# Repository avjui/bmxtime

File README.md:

BMXTIME
=======

BMXTIME is a small programm for time measure. The development is in betaphase. The time measure can be done with some lightbarrier build with a Ardurino.

<hr />

Current Features are:

	* time stop 
	* otpional time between
	* add differnt driver for statistic

<hr />

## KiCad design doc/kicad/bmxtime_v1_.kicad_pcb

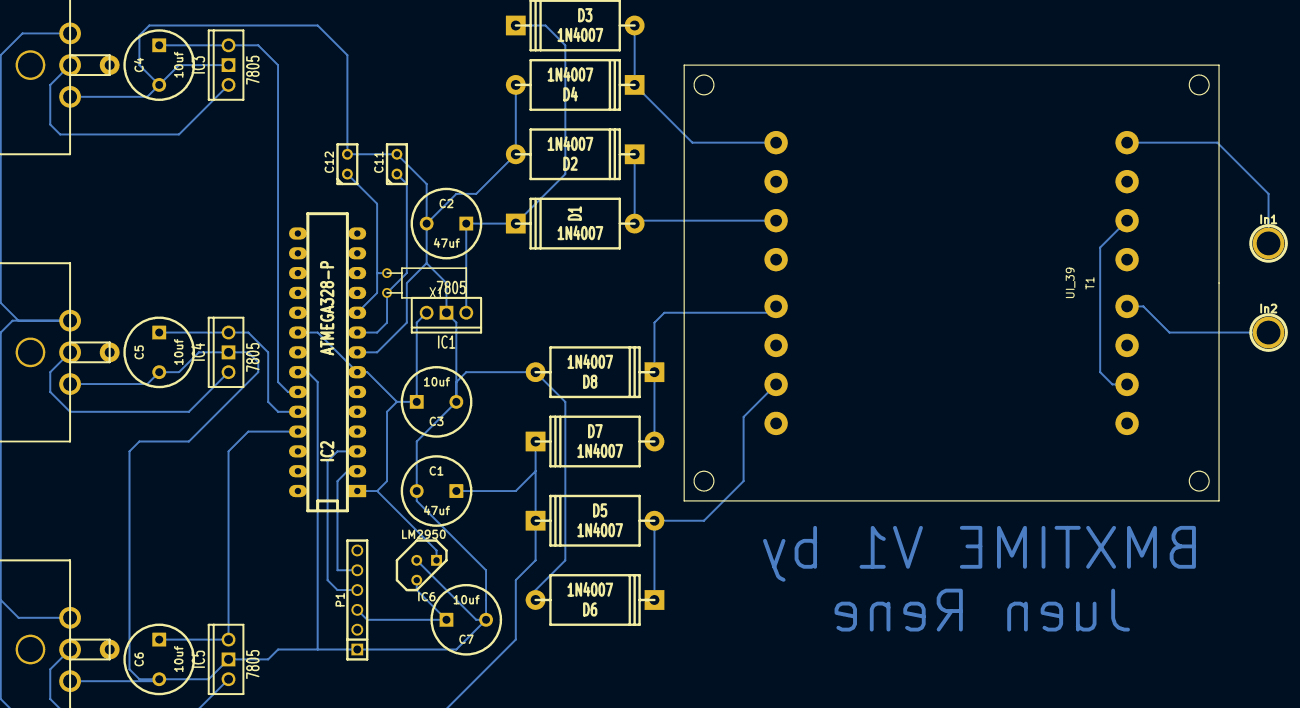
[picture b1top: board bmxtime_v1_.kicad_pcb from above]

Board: 2 copper layers, 31 parts (0 on the bottom side), 22 nets.

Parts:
C1, C2: 47uf; C2V8
C3, C4, C5, C6, C7: 10uf; C2V8
C11, C12: 22pf; C1
D1, D2, D3, D4, D5, D6, D7, D8: 1N4007; D6
IC1, IC3, IC4, IC5: 7805; LM78XXV
IC2: ATMEGA328-P; DIP-28__300_ELL
IC6: LM2950; LM2931
In1, In2: CONN_1; 1pin
K1, K2, K3: XLR3; XLR3MC
P1: CONN_SERIAL_SF; PIN_ARRAY-6X1
T1: UI_39; UI 39_Flachtransformator
X1: 16Mhz; QMONTRE

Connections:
/5V: C3.1, IC1.VO, IC2.1, IC2.7, IC2.20, IC6.1
unnamed: C5.1, IC2.24, IC4.VO
unnamed: D7.1, D8.2, T1.12
unnamed: IC2.3, P1.4
unnamed: C6.1, IC2.25, IC5.VO
unnamed: IC2.2, P1.5
unnamed: C7.1, IC6.2, P1.3
unnamed: D1.1, D2.2, T1.14
unnamed: T1.3, T1.7
unnamed: In2.1, T1.5
unnamed: In1.1, T1.1
unnamed: D5.1, D6.2, T1.10
unnamed: D3.1, D4.2, T1.16
unnamed: C2.1, D1.2, D3.2, IC1.VI
unnamed: C1.1, D5.2, D7.2, K1.1, K2.1, K3.1
unnamed: C1.2, C2.2, C3.2, C4.2, C5.2, C6.2, C7.2, C11.2, C12.2, D2.1, D4.1, D6.1, D8.1, IC1.GND, IC2.8, IC2.22, IC3.GND, IC4.GND, IC5.GND, IC6.3, K1.2, K2.2, K3.2, P1.1
unnamed: C12.1, IC2.10, X1.2
unnamed: C11.1, IC2.9, X1.1
unnamed: IC3.VI, K1.3
unnamed: C4.1, IC2.23, IC3.VO
unnamed: IC5.VI, K3.3
unnamed: IC4.VI, K2.3

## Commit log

2014-04-09 first code inital
2014-04-09 add setupfile
2014-04-21 Some more updates
2014-04-21 Update setup.py for exe creation
2014-04-21 Change the start up, because it give a warning
2014-05-21 Fix get_serial_ports function
2014-07-21 some fixes
    # Add logger
    # Fix several error with serial connection
    # Update gitignore
2014-07-21 update setup.py
    # remove bundle files
    # add manifest
2014-07-22 Make lists sortabele
2014-07-22 Update GetAllData function to return also time
    # Update sql command
    # also update the UpdateSortList function
2014-07-23 Update driverslist
    # add dialog for adding driver classes
    # add function for delete driver
2014-07-27 Make driverslist resizeable
    # add boxsizer
    # change resolution of dialog
    # change layout ( buttons come to the left side
2014-07-27 some updates
    # add Boxsizer
    # make led variable dynamic
2014-08-19 add some files
    # Schematic
    # PCB Layout
